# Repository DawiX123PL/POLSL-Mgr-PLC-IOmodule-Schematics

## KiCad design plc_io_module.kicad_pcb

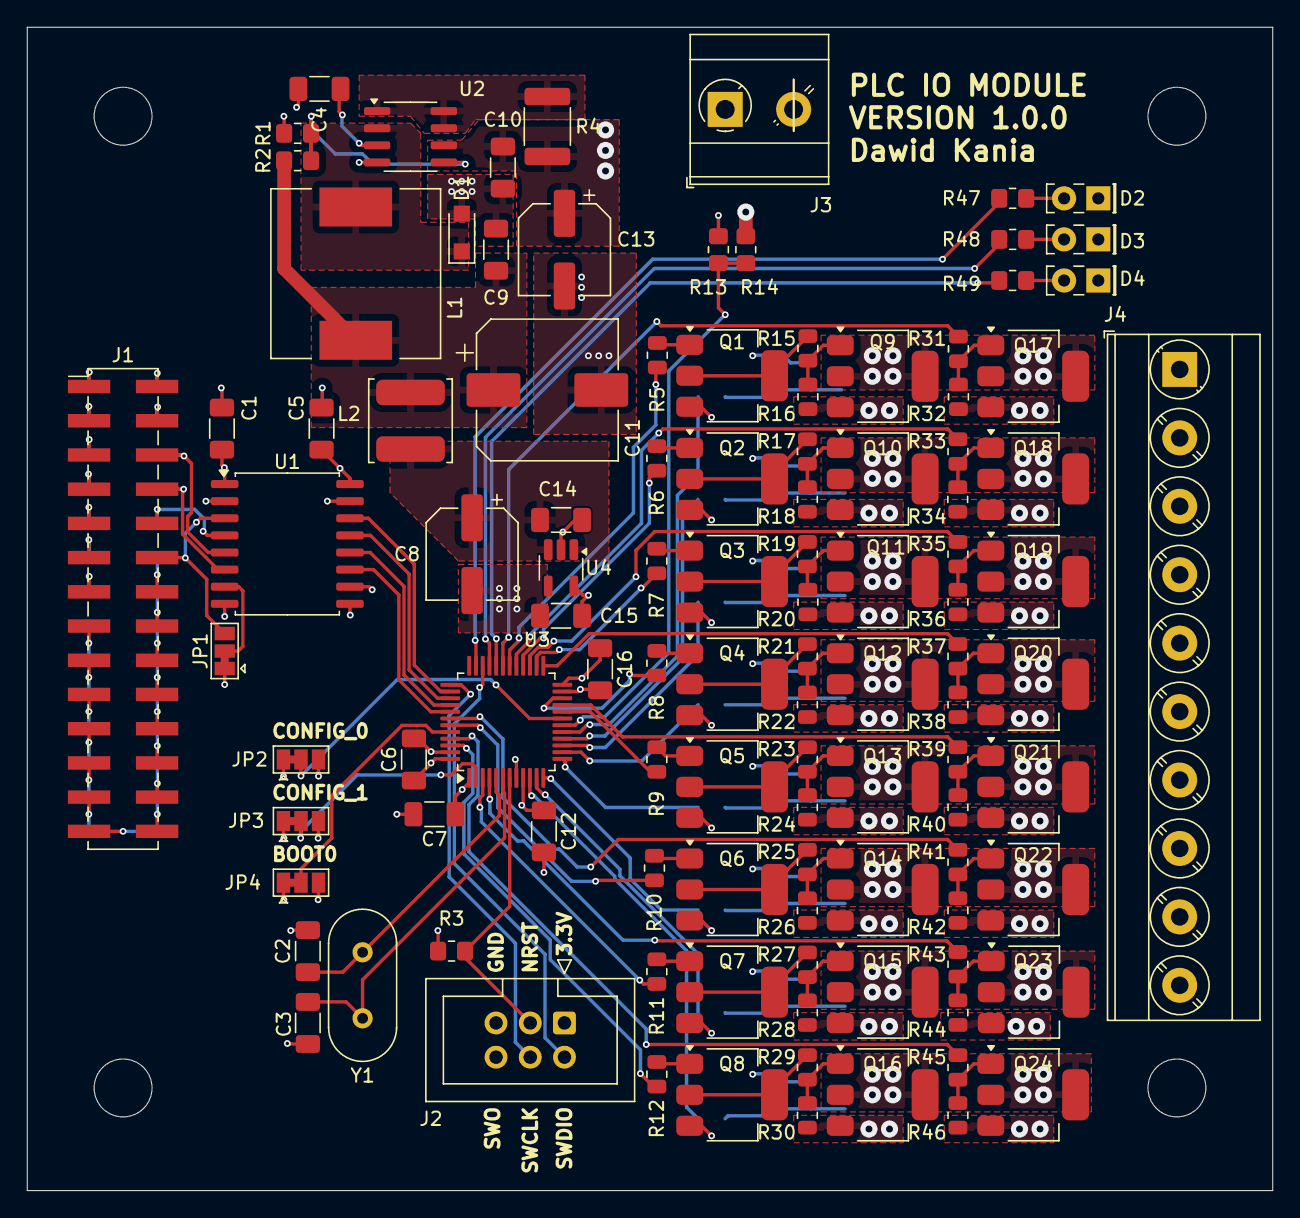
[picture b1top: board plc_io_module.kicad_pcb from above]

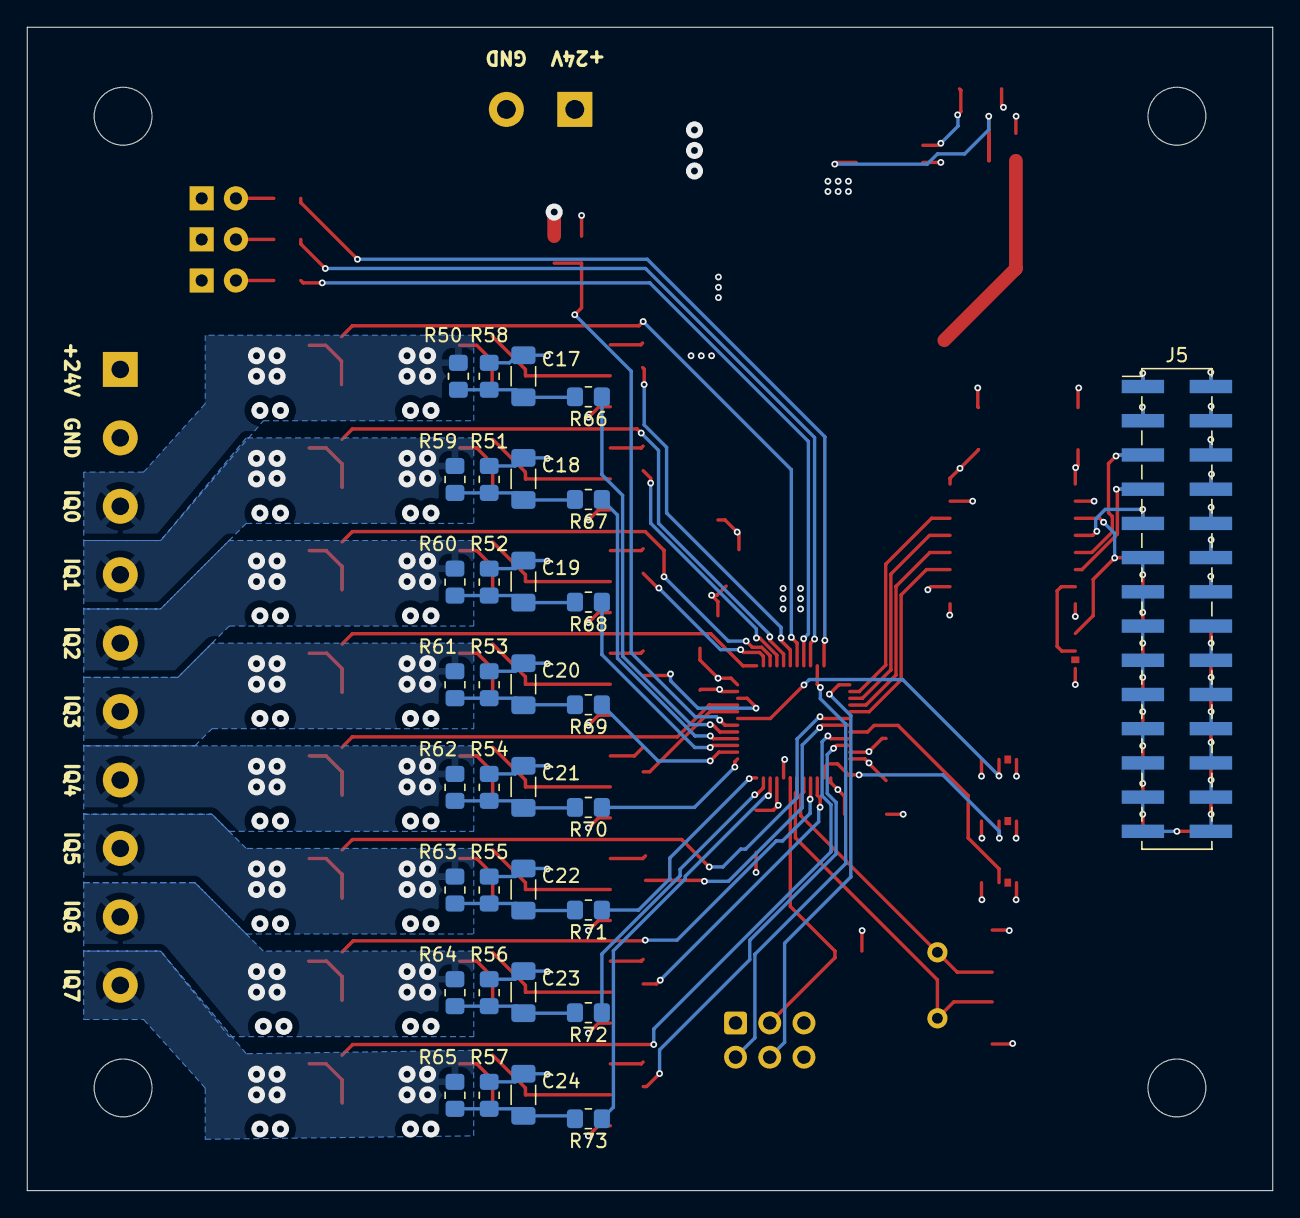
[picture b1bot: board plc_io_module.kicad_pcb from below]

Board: 4 copper layers, 92.5 x 86.4 mm, 145 parts (33 on the bottom side), 128 nets.

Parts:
C1, C2, C3, C5, C6, C7, C12, C16: 100nF; C_1206_3216Metric_Pad1.33x1.80mm_HandSolder
C4: 470pF; C_1206_3216Metric_Pad1.33x1.80mm_HandSolder
C8: 100uF 16V; CP_Elec_6.3x7.7
C9, C10, C14, C15: 10nF 25V; C_1206_3216Metric_Pad1.33x1.80mm_HandSolder
C11: 470uF 16V; CP_Elec_10x10
C13: 100uF 25V; CP_Elec_6.3x7.7
C17, C18, C19, C20, C21, C22, C23, C24: 1uF; C_1206_3216Metric_Pad1.33x1.80mm_HandSolder
D1: 1N5819; Nexperia_CFP3_SOD-123W
D2: LED_GREEN; LED_Rectangular_W5.0mm_H2.0mm
D3: LED_Orange; LED_Rectangular_W5.0mm_H2.0mm
D4: LED_RED; LED_Rectangular_W5.0mm_H2.0mm
H1, H2, H3, H4: MountingHole; MountingHole_4.3mm_M4
J1, J5: Conn_02x14_Odd_Even; PinHeader_2x14_P2.54mm_Vertical_SMD
J2: Conn_02x03_Odd_Even; IDC-Header_2x03_P2.54mm_Vertical
J3: Screw_Terminal_01x02; TerminalBlock_MetzConnect_Type073_RT02602HBLU_1x02_P5.08mm_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
J4: Screw_Terminal_01x10; TerminalBlock_Phoenix_MKDS-3-10-5.08_1x10_P5.08mm_Horizontal
JP1, JP2, JP3, JP4: SolderJumper_3_Bridged12; SolderJumper-3_P1.3mm_Bridged12_Pad1.0x1.5mm
L1: 220uH; L_12x12mm_H6mm
L2: 1.0uH; L_TDK_VLS6045EX_VLS6045AF
Q1, Q2, Q3, Q4, Q5, Q6, Q7, Q8, Q17, Q18, Q19, Q20, Q21, Q22, Q23, Q24: BCP5516T; SOT-223-3_TabPin2
Q9, Q10, Q11, Q12, Q13, Q14, Q15, Q16: BCP5116TA; SOT-223-3_TabPin2
R1: 1.2k; R_0805_2012Metric_Pad1.20x1.40mm_HandSolder
R2: 3.6k; R_0805_2012Metric_Pad1.20x1.40mm_HandSolder
R3, R13, R58, R59, R60, R61, R62, R63, R64, R65, R66, R67, R68, R69, R70, R71, R72, R73: 10k; R_0805_2012Metric_Pad1.20x1.40mm_HandSolder
R4: 0.33R; R_1812_4532Metric_Pad1.30x3.40mm_HandSolder
R5, R6, R7, R8, R9, R10, R11, R12, R31, R33, R35, R37, R39, R41, R43, R45: 500R; R_0805_2012Metric
R14, R50, R51, R52, R53, R54, R55, R56, R57: 62k; R_0805_2012Metric_Pad1.20x1.40mm_HandSolder
R15, R17, R19, R21, R23, R25, R27, R29: 5k; R_0805_2012Metric
R16, R18, R20, R22, R24, R26, R28, R30, R32, R34, R36, R38, R40, R42, R44, R46: 100k; R_0805_2012Metric
R47, R48, R49: 300R; R_0805_2012Metric_Pad1.20x1.40mm_HandSolder
U1: ISO6741; SOIC-16W_7.5x10.3mm_P1.27mm
U2: MC34063AD; SOIC-8_3.9x4.9mm_P1.27mm
U3: STM32F030C6Tx; LQFP-48_7x7mm_P0.5mm
U4: TLV73333PDBV; SOT-23-5_HandSoldering
Y1: 8MHz; Crystal_HC18-U_Vertical

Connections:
+3.3V: C5.1, C6.1, C7.1, C12.1, C15.1, C16.1, J2.1, JP2.3 (B), JP3.3 (B), JP4.3 (B), R3.1, U1.10 (EN2), U1.16 (V_{CC2}), U3.1 (VDD), U3.9 (VDDA), U3.24 (VDD), U3.48 (VDD), U4.5 (OUT)
+3.3V isolated: C1.1, J1.3, J5.4, JP1.1 (A), U1.1 (V_{CC1})
+5V: C8.1, C14.1, L2.2, U4.1 (IN), U4.3 (EN)
+5V isolated: J1.1, J5.2
+24V: C10.1, C13.1, J3.1, J4.1, Q9.3 (E), Q10.3 (E), Q11.3 (E), Q12.3 (E), Q13.3 (E), Q14.3 (E), Q15.3 (E), Q16.3 (E), R4.1, R14.1, R16.1, R18.1, R20.1, R22.1, R24.1, R26.1, R28.1, R30.1, U2.6 (Vin)
CONFIG_0: JP2.2 (C), U3.19 (PB1)
CONFIG_1: JP3.2 (C), U3.2 (PC13)
CS0_I: J1.12, JP1.3 (B), U1.3 (INA)
CS1_I: J1.14, J5.11
CS2_I: J1.16, J5.13
CS3_I: J1.18, J5.15
CS4_I: J1.20, J5.17
CS5_I: J1.22, J5.19
CS6_I: J1.24, J5.21
CS7_I: J1.26, J5.23
CS8_I: J1.28, J5.25
CS9_I: J1.27, J5.27
CS10_I: J1.25, J5.28
CS11_I: J1.23, J5.26
CS12_I: J1.21, J5.24
CS13_I: J1.19, J5.22
CS14_I: J1.17, J5.20
CS15_I: J1.15, J5.18
DI0_input: R66.1, U3.17 (PA7)
DI1_input: R67.1, U3.16 (PA6)
DI2_input: R68.1, U3.15 (PA5)
DI3_input: R69.1, U3.14 (PA4)
DI4_input: R70.1, U3.13 (PA3)
DI5_input: R71.1, U3.12 (PA2)
DI6_input: R72.1, U3.11 (PA1)
DI7_input: R73.1, U3.10 (PA0)
DIQ0: J4.3, Q9.2 (C), Q17.2 (C), R50.1
DIQ1: J4.4, Q10.2 (C), Q18.2 (C), R51.1
DIQ2: J4.5, Q11.2 (C), Q19.2 (C), R52.1
DIQ3: J4.6, Q12.2 (C), Q20.2 (C), R53.1
DIQ4: J4.7, Q13.2 (C), Q21.2 (C), R54.1
DIQ5: J4.8, Q14.2 (C), Q22.2 (C), R55.1
DIQ6: J4.9, Q15.2 (C), Q23.2 (C), R56.1
DIQ7: J4.10, Q16.2 (C), Q24.2 (C), R57.1
DQ0_High: R5.1, U3.30 (PA9)
DQ0_Low: R31.1, U3.31 (PA10)
DQ1_High: R6.1, U3.28 (PB15)
DQ1_Low: R33.1, U3.29 (PA8)
DQ2_High: R7.1, U3.26 (PB13)
DQ2_Low: R35.1, U3.27 (PB14)
DQ3_High: R8.1, U3.22 (PB11)
DQ3_Low: R37.1, U3.25 (PB12)
DQ4_High: R9.1, U3.20 (PB2)
DQ4_Low: R39.1, U3.21 (PB10)
DQ5_High: R10.1, U3.43 (PB7)
DQ5_Low: R41.1, U3.42 (PB6)
DQ6_High: R11.1, U3.3 (PC14)
DQ6_Low: R43.1, U3.4 (PC15)
DQ7_High: R12.1, U3.46 (PB9)
DQ7_Low: R45.1, U3.45 (PB8)
GND: C2.2, C3.2, C4.2, C5.2, C6.2, C7.2, C8.2, C9.2, C10.2, C11.2, C12.2, C13.2, C14.2, C15.2, C16.2, C17.2, C18.2, C19.2, C20.2, C21.2, C22.2, C23.2, C24.2, D1.2 (A), D2.1 (K), D3.1 (K), D4.1 (K), J2.5, J3.2, J4.2, JP2.1 (A), JP3.1 (A), JP4.1 (A), Q1.3 (E), Q2.3 (E), Q3.3 (E), Q4.3 (E), Q5.3 (E), Q6.3 (E), Q7.3 (E), Q8.3 (E), Q17.3 (E), Q18.3 (E), Q19.3 (E), Q20.3 (E), Q21.3 (E), Q22.3 (E), Q23.3 (E), Q24.3 (E), R1.2, R13.2, R32.1, R34.1, R36.1, R38.1, R40.1, R42.1, R44.1, R46.1, R58.2, R59.2, R60.2, R61.2, R62.2, R63.2, R64.2, R65.2, U1.9 (GND2), U1.15 (GND2), U2.4 (GND), U3.8 (VSSA), U3.23 (VSS), U3.47 (VSS), U4.2 (GND)
GND isolated: C1.2, J1.2, J1.4, J5.1, J5.3, U1.2 (GND1), U1.8 (GND1)
LED_GREEN: R47.1, U3.35 (PF6)
LED_ORANGE: R48.1, U3.33 (PA12)
LED_RED: R49.1, U3.32 (PA11)
MISO_I: J1.6, J5.5, U1.5 (INC)
MOSI_I: J1.8, J5.7, U1.6 (OUTD)
NRST: J2.3, R3.2, U3.7 (NRST)
unnamed: C9.1, C11.1, L1.2, L2.1, R2.1
unnamed: C17.1, R50.2, R58.1, R66.2
unnamed: C18.1, R51.2, R59.1, R67.2
unnamed: C19.1, R52.2, R60.1, R68.2
unnamed: C20.1, R53.2, R61.1, R69.2
unnamed: C21.1, R54.2, R62.1, R70.2
unnamed: C22.1, R55.2, R63.1, R71.2
unnamed: C23.1, R56.2, R64.1, R72.2
unnamed: C24.1, R57.2, R65.1, R73.2
unnamed: D1.1 (K), L1.1, U2.2 (SwE)
unnamed: D2.2 (A), R47.2
unnamed: D3.2 (A), R48.2
unnamed: D4.2 (A), R49.2
unnamed: JP1.2 (C), U1.7 (EN1)
unnamed: JP4.2 (C), U3.44 (BOOT0)
unnamed: Q1.1 (B), R5.2
unnamed: Q1.2 (C), R15.2
unnamed: Q2.1 (B), R6.2
unnamed: Q2.2 (C), R17.2
unnamed: Q3.1 (B), R7.2
unnamed: Q3.2 (C), R19.2
unnamed: Q4.1 (B), R8.2
unnamed: Q4.2 (C), R21.2
unnamed: Q5.1 (B), R9.2
unnamed: Q5.2 (C), R23.2
unnamed: Q6.1 (B), R10.2
unnamed: Q6.2 (C), R25.2
unnamed: Q7.1 (B), R11.2
unnamed: Q7.2 (C), R27.2
unnamed: Q8.1 (B), R12.2
unnamed: Q8.2 (C), R29.2
unnamed: Q9.1 (B), R15.1, R16.2
unnamed: Q10.1 (B), R17.1, R18.2
unnamed: Q11.1 (B), R19.1, R20.2
unnamed: Q12.1 (B), R21.1, R22.2
unnamed: Q13.1 (B), R23.1, R24.2
unnamed: Q14.1 (B), R25.1, R26.2
unnamed: Q15.1 (B), R27.1, R28.2
unnamed: Q16.1 (B), R29.1, R30.2
unnamed: Q17.1 (B), R31.2, R32.2
unnamed: Q18.1 (B), R33.2, R34.2
unnamed: Q19.1 (B), R35.2, R36.2
unnamed: Q20.1 (B), R37.2, R38.2
unnamed: Q21.1 (B), R39.2, R40.2
unnamed: Q22.1 (B), R41.2, R42.2
unnamed: Q23.1 (B), R43.2, R44.2
unnamed: Q24.1 (B), R45.2, R46.2
unnamed: R4.2, U2.1 (SwC), U2.7 (Ipk), U2.8 (DC)
unnamed: C4.1, U2.3 (TC)
unnamed: R1.1, R2.2, U2.5 (Vfb)
unnamed: C2.1, U3.5 (PF0), Y1.1
unnamed: C3.1, U3.6 (PF1), Y1.2
SCK_I: J1.10, J5.9, U1.4 (INB)
SIG0_I: J1.5, J5.6
SIG1_I: J1.7, J5.8
SIG2_I: J1.9, J5.10
SIG3_I: J1.11, J5.12
SIG4_I: J1.13, J5.14
SPI_CS0: U1.14 (OUTA), U3.38 (PA15)
SPI_MISO: U1.12 (OUTC), U3.40 (PB4)
SPI_MOSI: U1.11 (IND), U3.41 (PB5)
SPI_SCK: U1.13 (OUTB), U3.39 (PB3)
SWCLK: J2.4, U3.37 (PA14)
SWDIO: J2.2, U3.34 (PA13)
V_SENSE: R13.1, R14.2, U3.18 (PB0)

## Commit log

2024-05-10 Create Schematic and PCB Design
2024-05-10 Fix minor issues
2024-05-10 Generate Fabrication Output files
2024-05-13 Update fabrication files
2024-05-17 Generate TME BOM files
2024-11-05 fix problems
